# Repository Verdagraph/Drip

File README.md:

<!-- PROJECT SHIELDS -->
<!--
*** I'm using markdown "reference style" links for readability.
*** Reference links are enclosed in brackets [ ] instead of parentheses ( ).
*** See the bottom of this document for the declaration of the reference variables
*** https://www.markdownguide.org/basic-syntax/#reference-style-links
-->

[![Version][version-shield]][version-url]
[![Issues][issues-shield]][issues-url]
[![Pull Requests][prs-shield]][prs-url]

<!-- PROJECT LOGO -->
<br />
<div align="center">

<h3 align="center">Verdagraph - Web Application</h3>

  <p align="center">
    A garden productivity tool, agro-ecology model, and IoT platform
    for a sustainable and cooperative future.
    <br />
    <!-- 
    <a href=""><strong>Try it yourself »</strong></a>
    <br />
    -->
    <br />
    <a href="https://verdagraph.org">Documentation</a>
    <!-- 
    ·
    <a href="https://youtu.be/jGFHhRVdxRM">YouTube</a>
    ·
    <a href="">Donate</a>
    --> 
    <br />
  </p>
</div>

See the [main project readme](https://github.com/Verdagraph) for background on this repository.

The Drip is an IoT irrigation controller intended to automate the management of fixed-pressure water supplies along with variable-pressure / gravitypfed rain catchement systems. Its current scope is to control dispensing water from one rain barrel and one fixed pressure supply, using a flow meter to track precise targets, and a pressure sensor to track the water level of the catchement system, and an ESP32.

This repository contains the ESP-IDF firmware, PCB design, BOM, and instructions for setting up the system. 

Possible improvements, in no particular order:
    - Creating a solar charging version with included circuitry and deep sleep mode.
    - Support using more than one of each type of water supply.
    - Control 12V pumps in case gravity-fed isn't possible.

## PCB Design

## Firmware Design

# Contributing

See the [contributing](./contributing.md) for instructions on contributing and setting up the development environment.

<!-- MARKDOWN LINKS & IMAGES -->
<!-- https://www.markdownguide.org/basic-syntax/#reference-style-links -->

<!-- IN-REPO -->

[version-shield]: https://img.shields.io/badge/version-0.0.1-blue?style=for-the-badge
[version-url]: https://github.com/Verdagraph/Drip/releases
[issues-shield]: https://img.shields.io/github/issues/Verdagraph/Drip.svg?style=for-the-badge
[issues-url]: https://github.com/Verdagraph/Drip/issues
[prs-shield]: https://img.shields.io/github/issues-pr/Verdagraph/Drip.svg?style=for-the-badge
[prs-url]: https://github.com/Verdagraph/Drip/pulls
[license-shield]: https://img.shields.io/github/license/Verdagraph/Drip.svg?style=for-the-badge
[license-url]: https://github.com/Verdagraph/Drip/LICENSE.txt

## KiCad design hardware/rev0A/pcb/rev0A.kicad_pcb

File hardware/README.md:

# PCB Design

https://www.electronics-tutorials.ws/blog/relay-switch-circuit.html
https://www.digikey.ca/en/blog/logic-level-shifting-basics  

There's two main type of pressure transducers: ones that have two wires and output a current, and ones that have 3 wires and output a voltage.
We can use the first type by adding a resistor with a known value to the path. Because we know the sensor is outputting a given current, and we know that the resistor must dissipate all the voltage before it as its connected to ground, we can take the voltage before the resistor and connect it to our ADC for a measurements.
The resistor is commonly 250 ohms which translates to 1-5V. For the voltage type, it is as simple as connecting the voltage to the ADC. For the current type, we measure the voltcage through a 10k ohm resistor, and remember that the 250 ohm resistor must sink the power (THT). We use a 220 ohm to give a little margin for error.

The reset button is connected to the CHIP_PU or chip power up pin on the ESP. It is pulled up by default, enabling the MCU. When the button is pressed it is pulled to GND, with a small filtering capacitor to smooth it out, and the device resets.

The boot button is connectod to GPIO9. When GPIO0 is pulled high, the chip will boot into its saved program. When its pulled low, it will enter into the USB/UART boot mode. This person (https://www.instructables.com/Build-Custom-ESP32-Boards-From-Scratch-the-Complet/) also added a pullup here and found it reduced boot errors.

The USBC receptable connects the positive and negative data terminals on either side together and shunts them along with the USB bus voltage with zener diodes for ESD protection and the schtokky diode on the voltage line for reverse current protection, along with a filtering capacitor. THe CC1 and CC2 lines are pulled down for USBC functinoality

To the microcontroller: the power line is again filtered so that the voltage regulators can be farther from the rest. The chip_pu is pulled up again and filtered. The USB data lines are filtered again as well. There is a common bug in the devkits where because the CHIP_EN pin is used to reset the chip, and the GPIO9 pin is used to select the boot mode, the GPIO9 pin must be high at least 3ms before the CHIP_EN pin to avoid puttin the board in boot. To accomplish this, we add a pullup to GPIO9 to get around the weak internal pullup. This works because the GPIO9 is pulled up to the 3v3 output of the regulator, but the CHIP_EN is only brouhgut up once the ESP's 3v3 rail stabalizes, and it has extra filtering capacitors so it takes longer.

Our 12v-5v regulator is a switching buck converter LM2575, the fixed 5V output version. According to the typical application circuit, it has a filtering capacitor on the input, an LC filter on the output. There is also a schtokky diode to ground which allows a path for the inductor transient response to dissipate. To choose the L we follow the datasheet. Vin - Vout = 12-5 = 7. Vin - Vout * Vout / Vin * 1000 / 52 = 56V x us. We use the figure 12 to find the intersection of this and 1A means 220uH is  good. To choose output cap we use the formula in the datasheet which yields 56 uF. This is only for stability though. For ripple We round up to 330. 

the 5V to 3.3V regulator is the AMS1117 linear regulator and it has the same 2 capacitor filter on either end with a power LED.

The relays. These are 5 terminal 5V relay modules. The coils need 5V and 360mw to turn on so they need .36 / 5 = 72ma to run. Except the CE has voltage at saturation so we factor in a 0.7V drop. We also double the minimum current we need to make sure it works which gives us 167mA. We need to drive it with a transistor to get the 5V signal. The relay has a flyback diode. We use the BC337 but assume the transistor to have abeta of at least 100 which will cover common transistors at these conditions. This gives us a base current of 1.67mA. Given we're using 3.3v to run this that means the voltage across the resistor must be (3.3V - VBE) = 3.3 - 1.2 (which is the max BE voltage on the BC337 and 2n2222a) = 2.1V. R = V / I = 2.1V / 1.67ma = 1254ohm rounded to 1000.

The flow sensor: we use the TX20102 logic level shifter to go between the 5V pulses of the flow sensor and the 3.3V logic of the ESP. The enable pin is pulled down and connected to a GPIO so we can disable the pulses into the microcontroller when we don't care about the flow. We also have 0.1uF filters to stabailize the reference voltages as much as possible.

The ADC is the ADC088S022, as the ESP ADC is not reliable. This has both the 5V and 3.3V lines as the analog and digital power lines with filtering. The I2C is used to communicate with the ESP, while the power lines are filted as well. The max that we can go on any input is the analog supply + 0.3V, meaning we shouldn't make it go beyond 5.3V

https://www.aliexpress.com/item/1005006568129795.html?spm=a2g0o.productlist.main.25.45f354a8S2jKQZ&algo_pvid=02c4b3cc-5f71-485b-a4de-3bd9254a7f95&algo_exp_id=02c4b3cc-5f71-485b-a4de-3bd9254a7f95-24&pdp_ext_f=%7B%22order%22%3A%2298%22%2C%22eval%22%3A%221%22%7D&pdp_npi=4%40dis%21CAD%2150.61%2146.85%21%21%2135.71%2133.06%21%402101eac917449551732753582e5d94%2112000037696338130%21sea%21CA%210%21ABX&curPageLogUid=sR35G4mEGZbu&utparam-url=scene%3Asearch%7Cquery_from%3A

Power profiles:
ESP32c3 wroom 02: max 345A

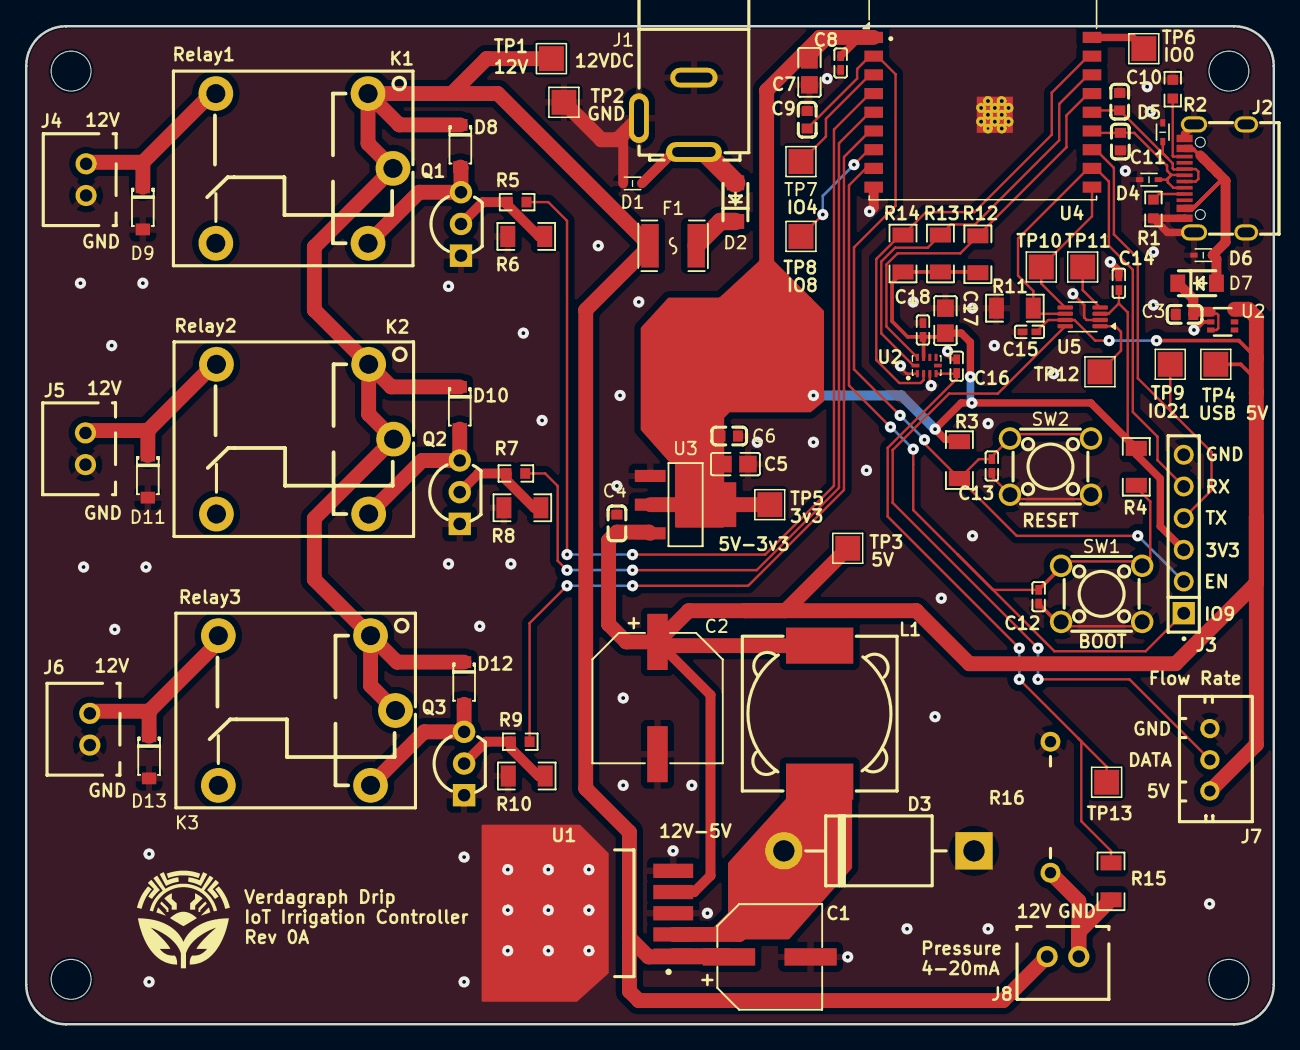
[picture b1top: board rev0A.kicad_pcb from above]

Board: 2 copper layers, 100.0 x 80.0 mm, 84 parts (0 on the bottom side), 41 nets.

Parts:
C1: 100uF; CAP-SMD_BD8.0-L8.3-W8.3-FD
C2: 330uF; CAP-SMD_BD10.0-L10.3-W10.3-LS11.3-FD
C3, C4, C6, C9: 1uF; C0603
C5, C7, C17: 10uF; C0805
C8, C12, C13, C14, C15, C16, C18: 0.1uF; C0402
C10, C11: 22pF; C0603
D1, D4, D5, D6: LESD5D5.0CT1G; SOD-523_L1.2-W0.8-LS1.6-BI
D2, D7: MBR230LSFT1G; SOD-123FL_L2.8-W1.8-LS3.6-RD
D3: 1N5822; DO-201AD_BD5.3-L8.4-P12.50-D1.4-FD
D8, D9, D10, D11, D12, D13: 1N4148W; SOD-123_L2.8-W1.8-LS3.7-RD
F1: 1A; F1812
J1: EJ508A; DC-IN-TH_EJ508A
J2: TYPE-C-31-M-12; USB-C_SMD-TYPE-C-31-M-12
J3: 6 Pin Socket Header; HDR-TH_6P-P2.54-V-F
J4, J5, J6, J8: 2 Pin JST; CONN-TH_B2B-XH-A-LF-SN
J7: 3 Pin JST; CONN-TH_3P-P2.50_A2501WV2-3P
K1, K2, K3: SRD-12VDC-SL-C; RELAY-TH_SRD-XXVDC-XL-C
L1: 330uH; IND-SMD_L12.3-W12.3
Q1, Q2, Q3: BC337; TO-92-3_L4.8-W3.7-P2.54-R
R1, R2: 5100; R0603
R3, R4, R6, R8, R10, R11, R12, R13, R14, R15: 10000; R1206
R5, R7, R9: 1000; R0603
R16: 120; RES-TH_BD2.2-L6.5-P10.50-D0.6
SW1, SW2: SW_Push; SW-TH_4P-L6.0-W6.0-P4.50-LS6.5
TP1, TP2, TP6, TP7, TP8, TP9: TestPoint_Pad_2.0x2.0mm
TP3, TP4, TP5, TP10, TP11, TP12, TP13: TestPoint; TestPoint_Pad_2.0x2.0mm
U1: LM2575T-5.0; TO-263-5_L10.2-W8.9-P1.70-TL
U2: TPS22919QDCKRQ1; SC-70-6_L2.0-W1.3-P0.65-LS2.1-BR
U3: LDL1117S33R; SOT-223-4_L6.5-W3.5-P2.30-LS7.0-BR
U4: ESP32-C3-WROOM-02-H4; ESP32-C3-WROOM-02
U5: TXS0102DCU; VSSOP-8_2.3x2mm_P0.5mm
U6: ADS1115IRUGT; X2QFN-10_L2.0-W1.5-P0.50-TL_RUG0010B

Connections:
+3.3V: C5.1, C6.1, C7.2, C8.2, C14.2, C17.1, C18.1, J3.3, R3.1, R4.1, R12.2, R13.2, R14.2, TP5.1, U3.2 (VOUT), U3.4 (VOUT), U4.1 (3V3), U5.3 (VCCA), U6.8 (VDD)
+5V: C2.1, C4.1, C15.1, J7.1, L1.2, TP3.1, TP4.1, U1.4 (FB), U2.6 (VOUT), U3.3 (VIN), U5.7 (VCCB)
+12V: C1.1, D8.1 (K), D10.1 (K), D12.1 (K), F1.2, J8.1, K1.C1, K1.COM, K2.C1, K2.COM, K3.C1, K3.COM, TP1.1, U1.1 (VIN)
ADC Alert: R14.1, U4.17 (IO1), U6.2 (ALERT/RDY)
CHIP_PU: C9.1, C13.1, J3.2, R3.2, SW2.3, SW2.4, U4.2 (EN)
D+: C10.1, D5.2, J2.A6 (DP1), J2.B6 (DP2), U4.14 (IO19)
D-: C11.1, D4.2, J2.A7 (DN1), J2.B7 (DN2), U4.13 (IO18)
Flow Sensor Data: TP10.1, U4.10 (IO10), U5.5 (A1)
Flow Sensor Enable: J3.5, R11.2, U4.11 (IO20/RXD), U5.6 (OE)
GND: C1.2, C2.2, C3.2, C4.2, C5.2, C6.2, C7.1, C8.1, C9.2, C10.2, C11.2, C12.2, C13.2, C14.1, C15.2, C16.2, C17.2, C18.2, D1.1, D3.1 (A), D4.1, D5.1, D6.1, D9.2 (A), D11.2 (A), D13.2 (A), J1.2, J1.3, J2.A1 (GND), J2.A12 (GND), J2.B1 (GND), J2.B12 (GND), J2.S1 (SHIELD), J2.S2 (SHIELD), J2.S3 (SHIELD), J2.S4 (SHIELD), J3.6, J4.2, J5.2, J6.2, J7.3, Q1.1 (E), Q2.1 (E), Q3.1 (E), R1.2, R2.2, R6.2, R8.2, R10.2, R11.1, R16.2, SW1.1, SW1.2, SW2.1, SW2.2, TP2.1, U1.3 (GND), U1.5 (~ON/OFF), U1.6 (TAB(GND)), U2.2 (GND), U3.1 (GND), U4.9 (GND), U4.19 (GND), U5.2 (GND), U6.1 (ADDR), U6.3 (GND)
GPIO9: C12.1, J3.1, R4.2, SW1.3, SW1.4, U4.8 (IO9)
IO21: J3.4, TP9.1, U4.12 (IO21/TXD)
unnamed: D1.2, D2.2 (A), J1.1
unnamed: D2.1 (K), F1.1
unnamed: D3.2 (K), L1.1, U1.2 (OUT)
unnamed: D6.2, D7.2 (A), J2.A4 (VBUS), J2.A9 (VBUS), J2.B4 (VBUS), J2.B9 (VBUS)
unnamed: C3.1, D7.1 (K), U2.1 (IN), U2.3 (ON)
unnamed: D8.2 (A), K1.C2, Q1.3 (C)
unnamed: D9.1 (K), J4.1, K1.NO
unnamed: D10.2 (A), K2.C2, Q2.3 (C)
unnamed: D11.1 (K), J5.1, K2.NO
unnamed: D12.2 (A), K3.C2, Q3.3 (C)
unnamed: D13.1 (K), J6.1, K3.NO
unnamed: J2.A5 (CC1), R1.1
unnamed: J2.B5 (CC2), R2.1
unnamed: J7.2, U5.8 (B1)
unnamed: J8.2, R15.2, R16.1
unnamed: Q1.2 (B), R5.2, R6.1
unnamed: Q2.2 (B), R7.2, R8.1
unnamed: Q3.2 (B), R9.2, R10.1
unnamed: TP6.1, U4.18 (IO0)
unnamed: TP7.1, U4.3 (IO4)
unnamed: TP8.1, U4.7 (IO8)
unnamed: TP11.1, U5.4 (A2)
unnamed: TP12.1, U5.1 (B2)
unnamed: C16.1, R15.1, TP13.1, U6.4 (AIN0)
Relay1: R5.1, U4.4 (IO5)
Relay2: R7.1, U4.5 (IO6)
Relay3: R9.1, U4.6 (IO7)
SCLK: R13.1, U4.16 (IO2), U6.10 (SCL)
SDA: R12.1, U4.15 (IO3), U6.9 (SDA)

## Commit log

2023-03-25 First
2023-03-28 Network initialization
2023-03-29 Working on the config loading
2023-03-30 Added setting config file
2023-03-30 Half changed to pointers
2023-03-31 worked
2023-04-03 began dispensation
2023-04-03 Working on reporting. Need to fix mqtt_client extern
2023-04-04 mostly done drain process
2023-04-05 Started readme
2023-04-06 working on docs
2023-04-12 updated all the cads
2023-04-12 updated bulkhead to 1/4 poly
2023-04-12 update bulkhead to 1/4 poly
2023-04-12 bulkhead to 1/4 poly
2023-04-14 Added flow sensor calibration
2023-04-14 merghing
2023-04-16 Added equipment photos
2023-04-27 update docs and cads
2023-05-05 bug fixing
2023-06-01 began PCB
2025-04-13 PCB draft
2025-04-14 Added fsm diagram
2025-04-20 PCB Progress
2025-04-24 Completes most PCB routing
2025-04-25 Completes PCB and drafts firmware structure
2025-04-27 PCB needs some final polish, adds structure of FSM and other managers
2025-04-27 Structured valve setup
2025-04-28 Defined dispense structure
2025-04-28 Polishing valve manager
2025-04-29 Updates PCB and readmes
2025-04-29 Fixed readme and updated license
2025-05-06 Updated pcb screenshot
2025-06-27 Polishes PCB
2025-08-02 Rev0A of the PCB
2025-08-05 Updates firmware
2025-08-10 Binging up firmware
2025-11-11 Fills some more out
2025-11-11 Gets to build again
2025-11-12 Updated config file
2025-11-22 Trying to refine build system
2025-11-23 Switche d to Plantfor mi IDOO
2025-11-25 Added new message framework
2025-12-01 Working on FSM system
2025-12-04 Improved custom state machine system
2025-12-07 Improves build
2025-12-08 Improving valve manager
2025-12-20 Adds clang-tidy
2025-12-25 Removing platform io
2025-12-27 Restarting
2026-02-17 Beginning migration to esp idf no platformio
2026-06-28 Uncommited changes
